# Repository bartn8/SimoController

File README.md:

# SimoController

## An ATMEGA328P based gamepad controller

- **5 Digital buttons** (first two can be used as Analog pins)
- **25 Matrix buttons**
- **Gamepad HID Device**: four axis and 22 buttons for single gamepad or two axis and 11 buttons for double gamepad

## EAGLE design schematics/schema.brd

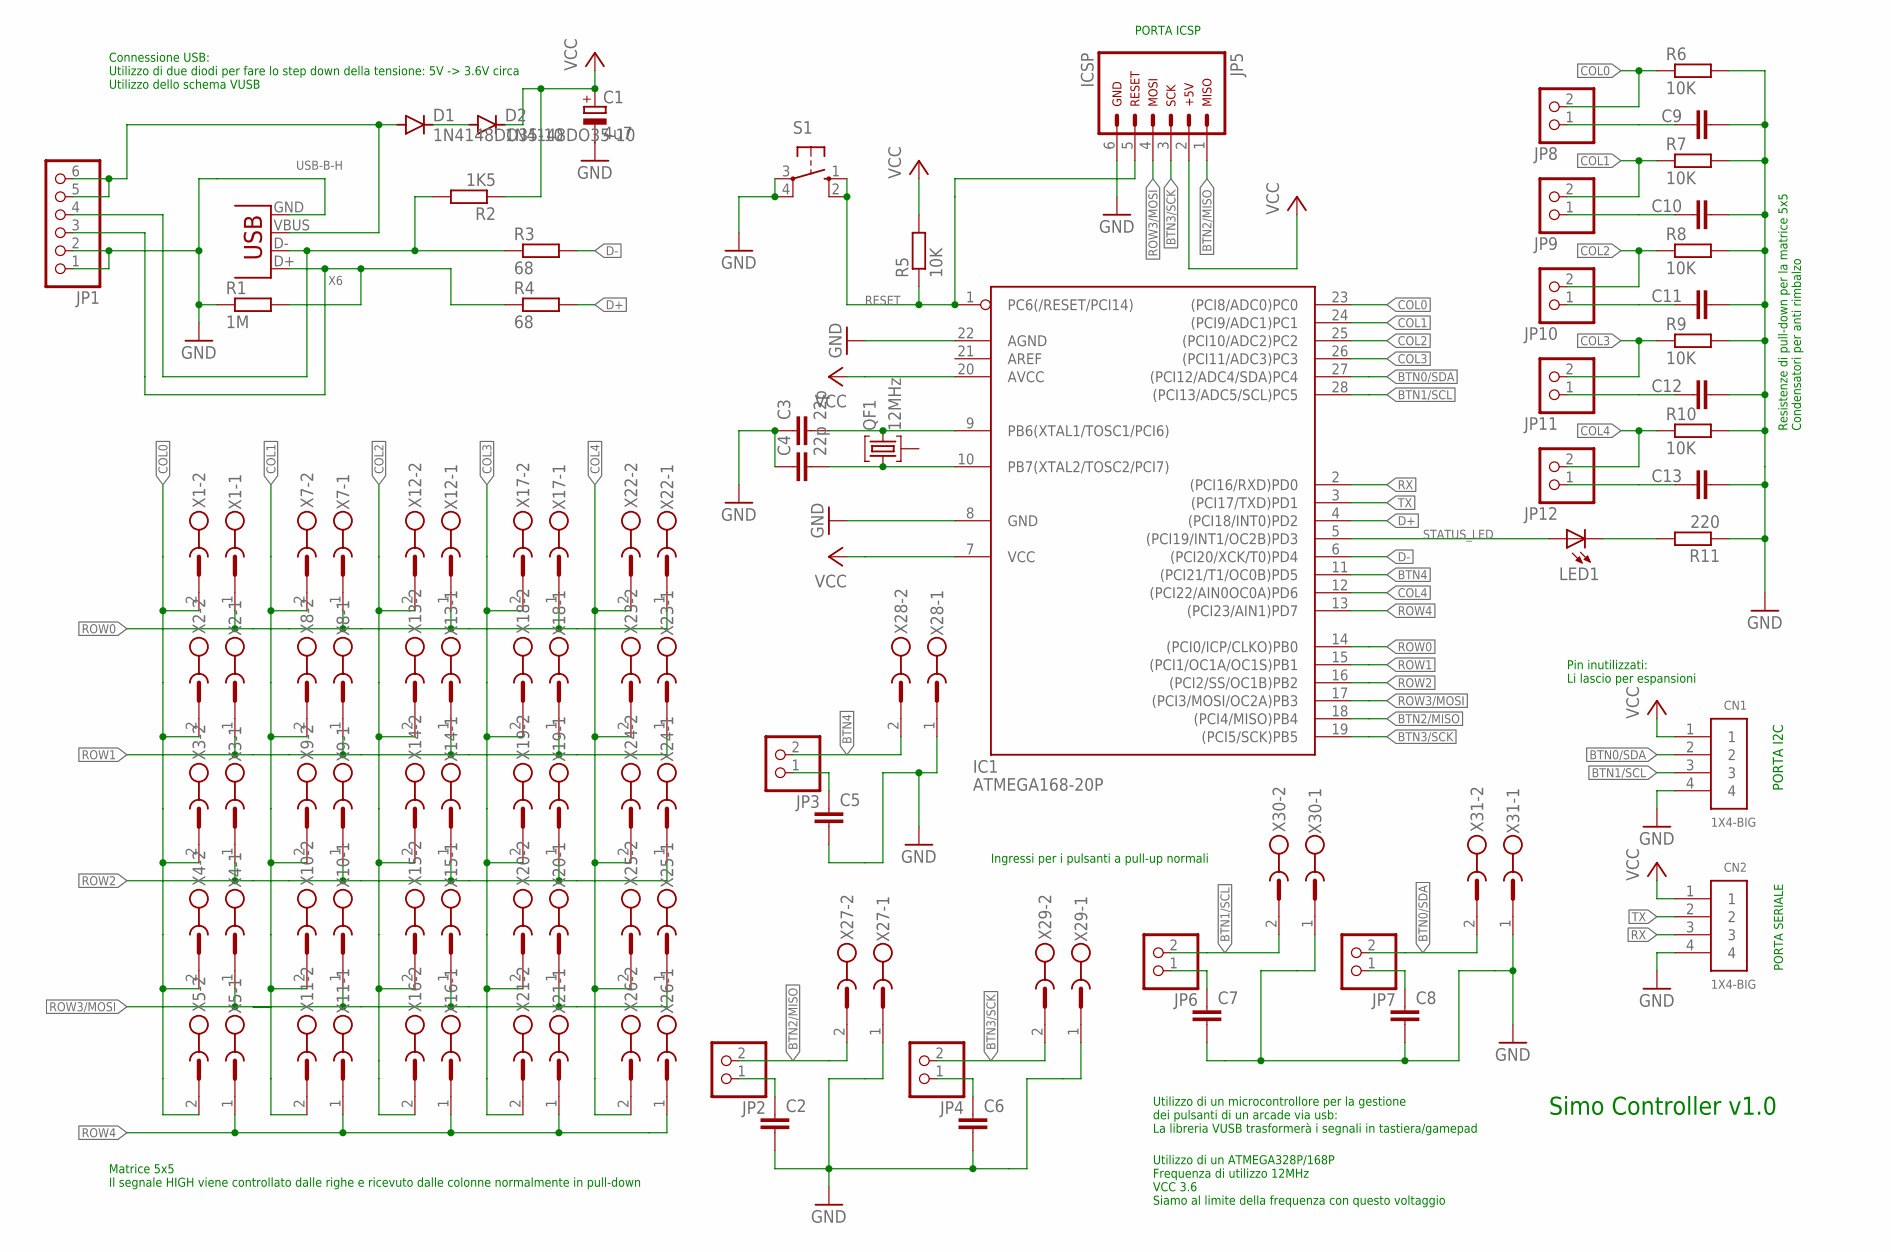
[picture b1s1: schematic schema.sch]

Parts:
C1: 4u7; E5-6
C2, C5, C6, C7, C8, C9, C10, C11, C12, C13: C-EU050-024X044; C050-024X044
C3, C4: 22p; C025-030X050
CN1, CN2: 1X4-BIG; 1X04-BIG
D1, D2: 1N4148DO35-10; DO35-10
IC1: ATMEGA168-20P; DIL28-3
JP1: PINHD-1X6; 1X06
JP2, JP3, JP4, JP6, JP7, JP8, JP9, JP10, JP11, JP12: PINHD-1X2; 1X02
JP5: ARDUINO_CONN-ICSP; CONN-2X03
LED1: LED3MM
QF1: 12MHz; HC49U
R1: 1M; 0309/12
R2: 1K5; 0309/12
R3, R4: 68; 0309/12
R5, R6, R7, R8, R9, R10: 10K; 0309/12
R11: 220; 0204/7
S1: 10-XX; B3F-10XX
X1, X2, X3, X4, X5, X7, X8, X9, X10, X11, X12, X13, X14, X15, X16, X17, X18, X19, X20, X21, X22, X23, X24, X25, X26, X27, X28, X29, X30, X31: MSTBV2
X6: USB-B-H

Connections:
BTN0/SDA: CN1.2, IC1.27 ((PCI12/ADC4/SDA)PC4), JP7.2, X31.2
BTN1/SCL: CN1.3, IC1.28 ((PCI13/ADC5/SCL)PC5), JP6.2, X30.2
BTN2/MISO: IC1.18 ((PCI4/MISO)PB4), JP2.2, JP5.1, X27.2
BTN3/SCK: IC1.19 ((PCI5/SCK)PB5), JP4.2, JP5.3, X29.2
BTN4: IC1.11 ((PCI21/T1/OC0B)PD5), JP3.2, X28.2
COL0: IC1.23 ((PCI8/ADC0)PC0), JP8.2, R6.1, X1.2, X2.2, X3.2, X4.2, X5.2
COL1: IC1.24 ((PCI9/ADC1)PC1), JP9.2, R7.1, X7.2, X8.2, X9.2, X10.2, X11.2
COL2: IC1.25 ((PCI10/ADC2)PC2), JP10.2, R8.1, X12.2, X13.2, X14.2, X15.2, X16.2
COL3: IC1.26 ((PCI11/ADC3)PC3), JP11.2, R9.1, X17.2, X18.2, X19.2, X20.2, X21.2
COL4: IC1.12 ((PCI22/AIN0OC0A)PD6), JP12.2, R10.1, X22.2, X23.2, X24.2, X25.2, X26.2
D+: IC1.4 ((PCI18/INT0)PD2), R4.2
D-: IC1.6 ((PCI20/XCK/T0)PD4), R3.2
GND: C1.-, C2.2, C3.1, C4.1, C5.2, C6.2, C7.2, C8.2, C9.2, C10.2, C11.2, C12.2, C13.2, CN1.4, CN2.4, IC1.8 (GND), IC1.22 (AGND), JP1.1, JP1.2, JP5.6, R1.1, R6.2, R7.2, R8.2, R9.2, R10.2, R11.1, S1.3, S1.4 (P1), X6.GND, X27.1, X28.1, X29.1, X30.1, X31.1
unnamed: D1.A, JP1.5, JP1.6, X6.VBUS
unnamed: D1.C, D2.A
unnamed: JP1.3, R1.2, R4.1, X6.D+
unnamed: JP1.4, R2.2, R3.1, X6.D-
unnamed: C3.2, IC1.9 (PB6(XTAL1/TOSC1/PCI6)), QF1.3
unnamed: C4.2, IC1.10 (PB7(XTAL2/TOSC2/PCI7)), QF1.1
unnamed: C5.1, JP3.1
unnamed: C9.1, JP8.1
unnamed: C10.1, JP9.1
unnamed: C2.1, JP2.1
unnamed: C6.1, JP4.1
unnamed: C7.1, JP6.1
unnamed: C8.1, JP7.1
unnamed: C11.1, JP10.1
unnamed: C12.1, JP11.1
unnamed: C13.1, JP12.1
unnamed: LED1.K (C), R11.2
RESET: IC1.1 (PC6(/RESET/PCI14)), JP5.5, R5.1, S1.1 (S), S1.2 (S1)
ROW0: IC1.14 ((PCI0/ICP/CLKO)PB0), X1.1, X7.1, X12.1, X17.1, X22.1
ROW1: IC1.15 ((PCI1/OC1A/OC1S)PB1), X2.1, X8.1, X13.1, X18.1, X23.1
ROW2: IC1.16 ((PCI2/SS/OC1B)PB2), X3.1, X9.1, X14.1, X19.1, X24.1
ROW3/MOSI: IC1.17 ((PCI3/MOSI/OC2A)PB3), JP5.4, X4.1, X10.1, X15.1, X20.1, X25.1
ROW4: IC1.13 ((PCI23/AIN1)PD7), X5.1, X11.1, X16.1, X21.1, X26.1
RX: CN2.3, IC1.2 ((PCI16/RXD)PD0)
STATUS_LED: IC1.5 ((PCI19/INT1/OC2B)PD3), LED1.A
TX: CN2.2, IC1.3 ((PCI17/TXD)PD1)
VCC: C1.+, CN1.1, CN2.1, D2.C, IC1.7 (VCC), IC1.20 (AVCC), JP5.2, R2.1, R5.2

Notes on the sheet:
Connessione USB: Utilizzo di due diodi per fare lo step down della tensione: 5V -> 3.6V circa Utilizzo dello schema VUSB
PORTA ICSP
PORTA SERIALE
Resistenze di pull-down per la matrice 5x5 Condensatori per anti rimbalzo
Ingressi per i pulsanti a pull-up normali
Matrice 5x5 Il segnale HIGH viene controllato dalle righe e ricevuto dalle colonne normalmente in pull-down
Utilizzo di un ATMEGA328P/168P Frequenza di utilizzo 12MHz VCC 3.6 Siamo al limite della frequenza con questo voltaggio
Pin inutilizzati: Li lascio per espansioni
Simo Controller v1.0
Utilizzo di un microcontrollore per la gestione dei pulsanti di un arcade via usb: La libreria VUSB trasformerà i segnali in tastiera/gamepad
PORTA I2C

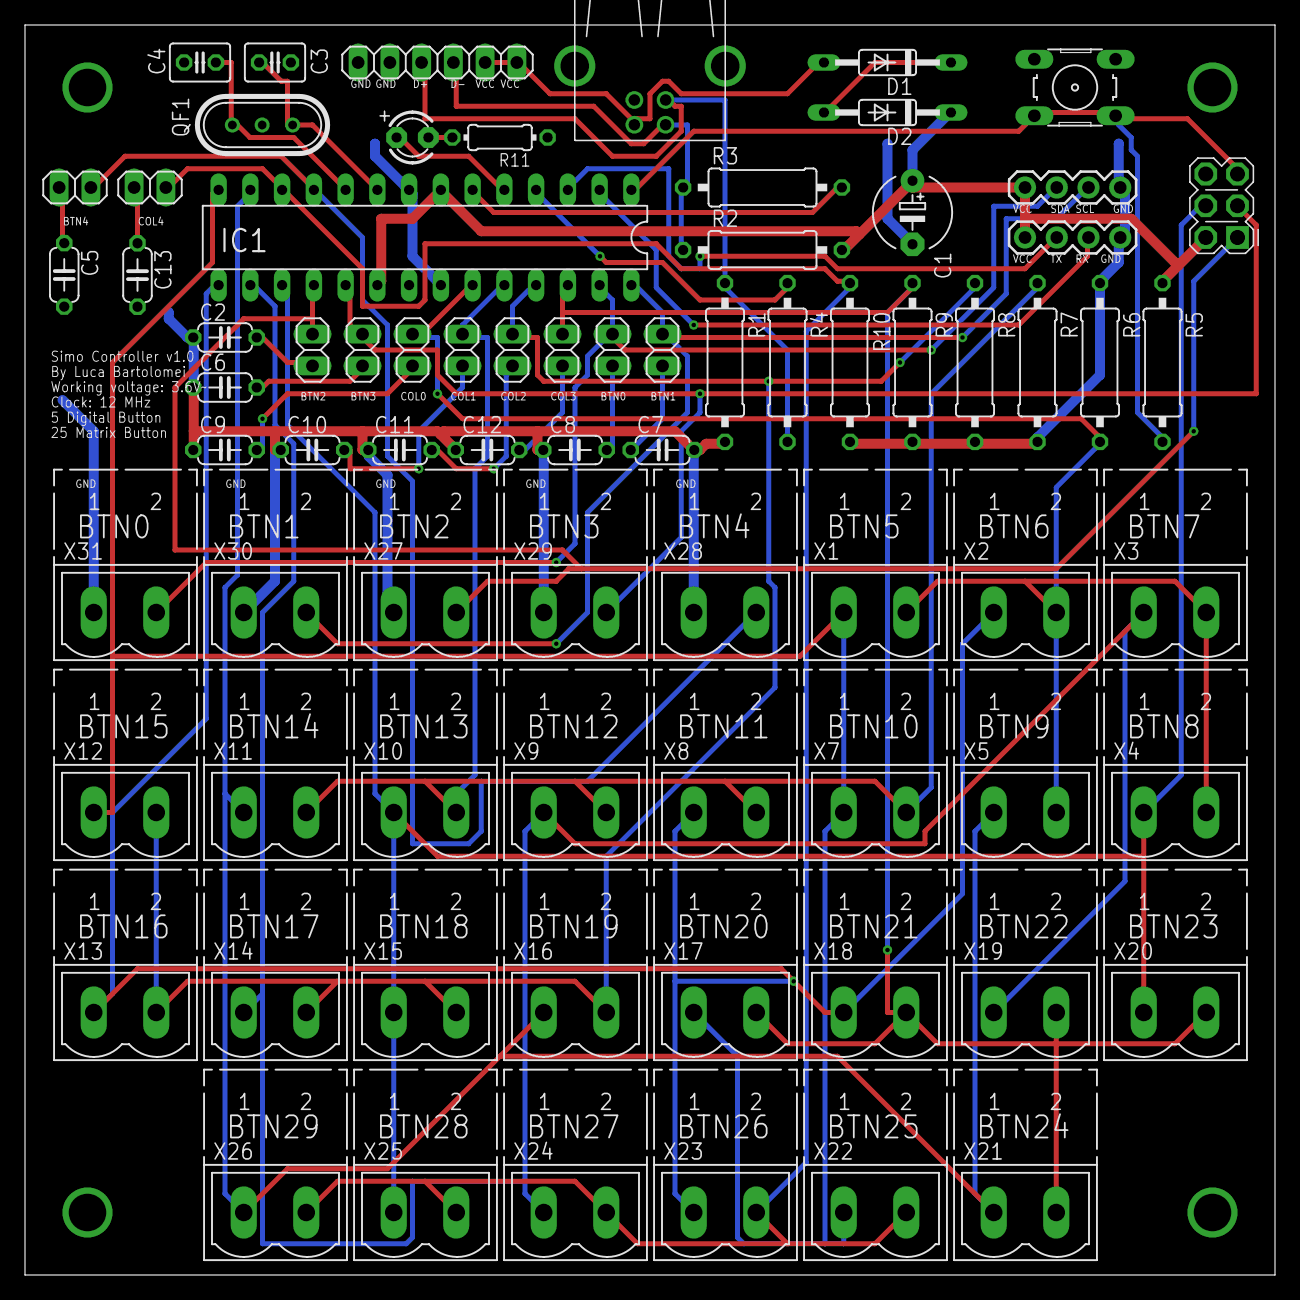
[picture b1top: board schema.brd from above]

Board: 2 copper layers, 100.0 x 100.0 mm, 75 parts (0 on the bottom side), 40 nets.

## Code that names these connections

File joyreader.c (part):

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
	//Matrix buttons needs external pull-down resistors.
	//BTN0-BTN4 use intenal pull-ups.
	PORTB |= (1 << PB4) | (1 << PB5);
	PORTC |= (1 << PC4) | (1 << PC5);
	PORTD |= (1 << PD5);


	//Initial state of buttons and matrix buttons
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	foundUpdate += updateButtonState(JOYREADER_GET_INDEX_BUTTON(JOYREADER_P_DIGITAL_4), (pinStateD & (1<<5)));
	
	//Matrix buttons
	//ROWS: PB0, PB1, PB2, PB3, PD7
	
	PORTB|=(1<<0);
	while(!(PINB & (1<<0)));
	
	//Check PC0, PC1, PC2, PC3, PD6
	pinStateC = PINC;
	pinStateD = PIND;
	
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	PORTB|=(1<<1);
	while(!(PINB & (1<<1)));
	
	//Check PC0, PC1, PC2, PC3, PD6
	pinStateC = PINC;
	pinStateD = PIND;
	
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	PORTB|=(1<<2);
	while(!(PINB & (1<<2)));
	
	//Check PC0, PC1, PC2, PC3, PD6
	pinStateC = PINC;
	pinStateD = PIND;
	
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	PORTB|=(1<<3);
	while(!(PINB & (1<<3)));
	
	//Check PC0, PC1, PC2, PC3, PD6
	pinStateC = PINC;
	pinStateD = PIND;
	
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	PORTD|=(1<<7);
	while(!(PIND & (1<<7)));
	
	//Check PC0, PC1, PC2, PC3, PD6
	pinStateC = PINC;
	pinStateD = PIND;
	
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
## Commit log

2020-09-03 Inital commit
    Schematics and photo are missing
2020-09-03 Added schematics and photo
2020-09-03 Different configurations of HID Report Descriptor
2020-09-03 Bug fix
2021-03-11 Bugfix (Not tested)
    Se si premono tutti i pulsanti contemporaneamente allora il dispositivo si resetta
    Provato a risolvere (non testato):
    - Watchdog time: 1sec -> 4sec
    - Riduzione finestra di accensione delle righe attraverso ottimizzazione (riduce il voltage drop)
    - Aumento del condensatore di VCC
    - Aumento delle resistenze di pull-down
